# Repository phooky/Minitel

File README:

General instructions for using the minitel over a serial port:

- Set up and open a serial connection to the minitel. If you've put the 
minitel in 4800 baud mode (say, with Fn-B 4), then:
  minicom -D /dev/ttyUSB0 -b 4800
  Leave the connection open by exiting with Ctrl-A J.
- Set the tty to do newline processing correctly
  stty opost onlcr icrnl </dev/ttyUSB0
- Run whatever
  adventure </dev/ttyUSB0 >/dev/ttyUSB0

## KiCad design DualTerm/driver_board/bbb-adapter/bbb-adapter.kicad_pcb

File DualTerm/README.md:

Framebuffer
===========

The tilcdc driver provides a framebuffer on /dev/fb0. The resolution of this
framebuffer is 320x256. 
LAST COLUMN MUST BE SET TO 0 TO AVOID A BRIGHT LINE DURING ENTIRE HORIZ. RETRACT

Create fb0:
echo "MINITEL-TILCDC" >>/sys/devices/platform/bone_capemgr/slots

Detatch the console on fb0:
echo 0 >/sys/class/vtconsole/vtcon1/bind

Disable screen blanking:
echo 0 >/sys/class/graphics/fb0/blank

fbpad is build to default to fb0.

KERNEL VERSION:
debian@beaglebone:~$ cat /proc/version 
Linux version 4.4.36-ti-r72 (root@a2-imx6q-wandboard-2gb) (gcc version 4.9.2 (Debian 4.9.2-10) ) #1 SMP Wed Dec 7 22:29:53 UTC 2016
debian@beaglebone:~$ lsb -a
-bash: lsb: command not found
debian@beaglebone:~$ lsb
lsblk        lsb_release  
debian@beaglebone:~$ lsb_release -a
No LSB modules are available.
Distributor ID: Debian
Description:    Debian GNU/Linux 8.6 (jessie)
Release:    8.6
Codename:   jessie

Warning: there is a newer version with missing capemgr!

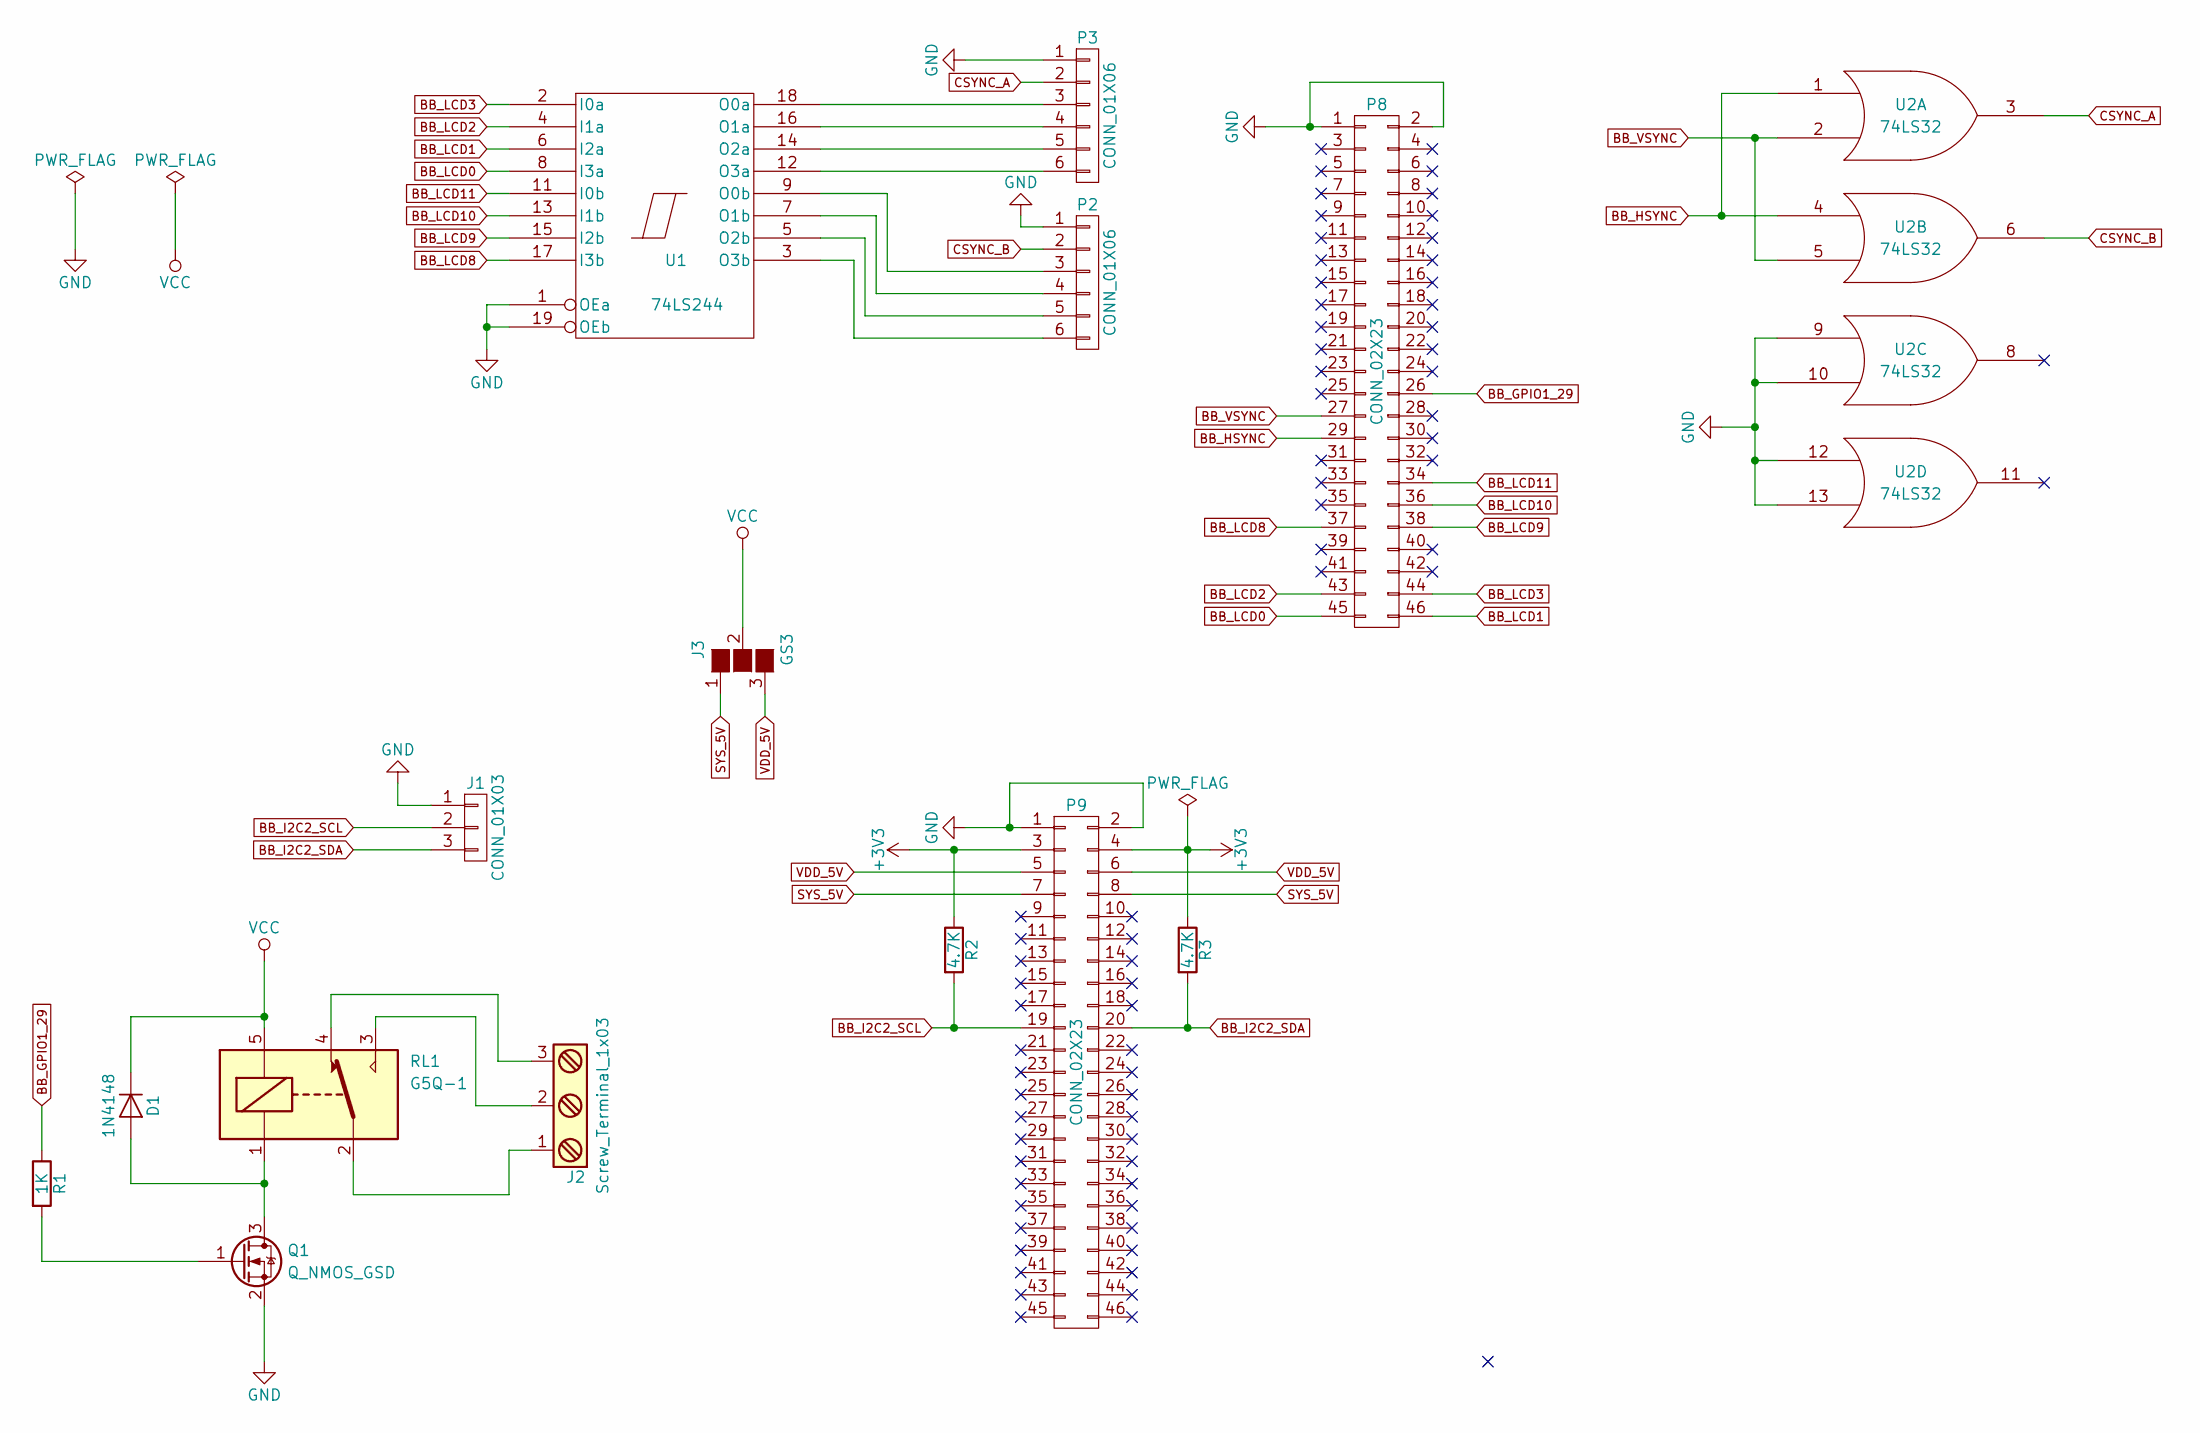
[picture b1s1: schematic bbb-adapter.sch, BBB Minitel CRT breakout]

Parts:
D1: 1N4148; D_DO-35_SOD27_P10.16mm_Horizontal
J1: CONN_01X03; Pin_Header_Angled_1x03_Pitch2.54mm
J2: Screw_Terminal_1x03; TerminalBlock_Pheonix_MKDS1.5-3pol
J3: GS3
P2, P3: CONN_01X06; Pin_Header_Angled_1x06_Pitch2.54mm
P8, P9: CONN_02X23; Pin_Header_Straight_2x23_Pitch2.54mm
Q1: Q_NMOS_GSD; SOT-23_Handsoldering
R1: 1K; R_Axial_DIN0207_L6.3mm_D2.5mm_P7.62mm_Horizontal
R2, R3: 4.7K; R_Axial_DIN0207_L6.3mm_D2.5mm_P7.62mm_Horizontal
RL1: G5Q-1; Relay_SPDT_OMRON-G5Q
U1: 74LS244; DIP-20_W7.62mm_LongPads
U2: 74LS32; DIP-14_W7.62mm_LongPads

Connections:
+3V3: P9.3, P9.4, R2.1, R3.1
BB_GPIO1_29: P8.26, R1.1
BB_HSYNC: P8.29, U2.1, U2.4
BB_I2C2_SCL: J1.2, P9.19, R2.2
BB_I2C2_SDA: J1.3, P9.20, R3.2
BB_LCD0: P8.45, U1.8 (I3a)
BB_LCD1: P8.46, U1.6 (I2a)
BB_LCD2: P8.43, U1.4 (I1a)
BB_LCD3: P8.44, U1.2 (I0a)
BB_LCD8: P8.37, U1.17 (I3b)
BB_LCD9: P8.38, U1.15 (I2b)
BB_LCD10: P8.36, U1.13 (I1b)
BB_LCD11: P8.34, U1.11 (I0b)
BB_VSYNC: P8.27, U2.2, U2.5
CSYNC_A: P3.2, U2.3
CSYNC_B: P2.2, U2.6
GND: J1.1, P2.1, P3.1, P8.1, P8.2, P9.1, P9.2, Q1.2 (S), U1.1 (OEa), U1.10 (GND), U1.19 (OEb), U2.7 (GND), U2.9, U2.10, U2.12, U2.13
unnamed: D1.2 (A), Q1.3 (D), RL1.1
unnamed: J2.1, RL1.2
unnamed: J2.2, RL1.3
unnamed: J2.3, RL1.4
unnamed: P2.3, U1.9 (O0b)
unnamed: P2.4, U1.7 (O1b)
unnamed: P2.5, U1.5 (O2b)
unnamed: P2.6, U1.3 (O3b)
unnamed: P3.3, U1.18 (O0a)
unnamed: P3.4, U1.16 (O1a)
unnamed: P3.5, U1.14 (O2a)
unnamed: P3.6, U1.12 (O3a)
unnamed: Q1.1 (G), R1.2
SYS_5V: J3.1 (G1), P9.7, P9.8
VCC: D1.1 (K), J3.2 (G2), RL1.5, U1.20 (VCC), U2.14 (VCC)
VDD_5V: J3.3 (G3), P9.5, P9.6

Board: 2 copper layers, 15 parts (0 on the bottom side), 33 nets, no tracks yet.

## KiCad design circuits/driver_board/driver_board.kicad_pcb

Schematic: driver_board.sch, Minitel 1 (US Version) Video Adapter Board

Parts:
C1: 10nF; C_Rect_L7.5_W6.5_P5
C2: 100nF; C_Rect_L7.5_W6.5_P5
CX1: COAX; COAX-SHLD
D1, D2, D3, D4: 1N4148; Diode_DO-35_SOD27_Horizontal_RM10
L1: 20uH; INDUCTOR_V
P1: CONN_01X06; Pin_Header_Angled_1x06
P2: CONN_01X07; CONN-1x7-5mm-pitch
Q1: C5468; TO-92_Inline_Wide
R1: 680; Resistor_Horizontal_RM10mm
R2: 4K; Resistor_Horizontal_RM10mm
R3: 1.8K; Resistor_Horizontal_RM10mm
R4: 1K; Resistor_Horizontal_RM10mm
R5: 460; Resistor_Horizontal_RM10mm
R6: 620; Resistor_Horizontal_RM10mm
R7: 100; Resistor_Horizontal_RM10mm
R8: 1.2K; Resistor_Horizontal_RM10mm
R9, R10: 2.4K; Resistor_Horizontal_RM10mm
RV1, RV2, RV3, RV4, RV5: POT; Potentiometer_Cermet_CT-6EP
U1: 74LS244; DIP-20_W7.62mm
U2: 74HC04; DIP-14_W7.62mm
U3: 7805; TO-220_Neutral123_Vertical

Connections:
GND: C1.1, C2.1, CX1.2, CX1.3, P1.1, P2.4, U1.1, U1.10, U1.13, U1.15, U1.17, U1.19, U2.7 (GND), U3.2
unnamed: C1.2, P2.2, R8.1
unnamed: C2.2, P2.1, R9.1, R10.1
unnamed: CX1.1, R7.1
unnamed: D1.1 (K), D2.1 (K), D3.1 (K), D4.1 (K), R1.2
unnamed: D1.2 (A), U1.18, U2.1
unnamed: D2.2 (A), U1.16, U2.3
unnamed: D3.2 (A), U1.14, U2.5
unnamed: D4.2 (A), U1.12, U2.9
unnamed: L1.1, Q1.2 (B)
unnamed: P1.2, U1.11
unnamed: P1.3, U1.8
unnamed: P1.4, U1.6
unnamed: P1.5, U1.4
unnamed: P1.6, U1.2
unnamed: P2.3, U2.12
unnamed: P2.6, U3.1
unnamed: Q1.1 (C), R7.2, R9.2, R10.2
unnamed: Q1.3 (E), R8.2, RV1.2, RV2.2, RV3.2, RV4.2, RV5.2
unnamed: R1.1, U2.11
unnamed: R2.1, RV1.1
unnamed: R2.2, U2.2
unnamed: R3.1, RV2.1
unnamed: R3.2, U2.4
unnamed: R4.1, RV3.1
unnamed: R4.2, U2.6
unnamed: R5.1, RV4.1
unnamed: R5.2, U2.8
unnamed: R6.1, RV5.1
unnamed: R6.2, U2.10
SYNC: U1.9, U2.13
VCC: L1.2, U1.20, U2.14 (VCC), U3.3

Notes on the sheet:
Pots are all 500 ohm CT6EP501 trimmers
Coil is Wurth 744772200
All resistors are standard 1/4W

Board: 2 copper layers, 29 parts (1 on the bottom side), 32 nets, no tracks yet.

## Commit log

2013-05-02 initial checkin
2013-05-02 adding basic doc
2013-05-02 don't resend redundant color information (speedup)
2013-05-02 turning minitel into a proper library adding unit tests to brush up on my tdd
2013-05-02 clearScreen
2013-05-02 convert over to object in script
2013-05-02 add newline
2013-05-02 added send and recv
2013-05-02 adding textmode switching
2013-05-02 added textmode test
2013-05-02 added and tested colors
2013-05-02 add vt mode switching
2013-05-02 cursor movement added
2013-05-02 fixup on test (text coords are 1-indexed)
2013-05-02 OMG MY SUBPIXEL ORDERING WAS OFF I AM SOOO EMBARRASSED
2013-05-03 tumblr image->minitel script
2013-05-06 reorganize image conversion in prep for menuing system
2013-05-07 adding screen reader
2013-05-07 move key to a json file
2013-05-23 added interactive mode added show/hide cursor added readline()
2013-05-25 update doc
2013-06-15 get port for command line
2013-06-15 oops; do port as env instead
2013-06-15 no sleep
2013-09-23 adding readme for general use
2013-09-27 adding cad files for NYCR "information terminal".
2013-09-27 adding top-level menuing system for minitel information service
2013-09-28 w/ curses emulation
2013-09-28 menuing system tested
2013-09-29 successfully running subprocesses (test case: /usr/games/adventure)
2013-09-29 added timeouts; default to 10 minutes without interaction.
2013-09-29 extend default timeout to ten minutes; test tinymush via terminal
2013-09-30 sim only if port is set to SIM
2013-09-30 default to ansi mode
2013-10-02 Update Readme.md
    Merged the information in README into this file
2013-10-02 Delete README
    Merged info into existing readme
2013-10-02 Update Readme.md
    Formatting
2013-10-02 adding cut file for top
2013-10-03 added support for various hax
2013-10-03 no room for wide, use tall
2013-10-03 move log to log
2013-10-04 lf/cr translation
2013-10-04 removing prints from library center title better colors
2013-10-04 adding game menu
2013-10-04 adding pager
2013-10-04 pager is running
2013-10-05 added sketch
2013-10-05 adding wakeup
2013-10-05 adding init script and readme
2013-10-05 run perpetually
2013-10-05 adding wait-for-key
2013-10-05 needed shell line
2013-10-05 fix pager keys, no 0 out of main menu, no immediate restart on timeout
2013-10-07 creating new format, parser
2013-10-08 menus working
2013-10-08 doc and screen up
2013-10-08 fix cli parse oops
2013-10-08 adding directions to pager
2013-10-08 clean up colors
2013-10-08 invalidate colors on clear; inverse text breadcrumbs
2013-10-08 adding runtime stuff again
2013-10-08 removing redundant file
2013-10-08 mode switching
2013-10-09 mode switching fixes
2013-10-09 minor fixups, cosmetic and otherwise
2013-10-10 added google calendar
2013-10-10 fixed run process
2013-10-11 refactoring tumblr for infoterm
2013-10-11 adding in tumblr screen
2013-10-12 adding maps
2013-10-12 cropped map
2013-10-12 adding non-scaling options
2013-10-13 change %screen to %layout
2013-10-13 removing timeout from menu
2013-10-13 adding layout class
2013-10-13 adding layout to type map
2013-10-13 B/W map to deal with color limitations
2013-10-13 testing, fixes for syntax issues, display issues
2013-10-13 adding echo key, test mode
2013-10-13 add 4 to test and kill extra keypress
2013-10-16 adding image caching (along with rep cache)
2013-10-16 fixed import
2013-10-18 fix calendar to handle private events
2013-10-18 ignore comments
2013-10-18 abbreviate pg
2013-10-18 reduce debug dump
2013-10-18 adding echo code
2013-12-01 update menus to add reboot
2017-04-05 adding video start
2017-04-07 continuing to reverse video output stage
2017-04-07 better video output stage diagram
2017-04-12 generated netlist; have actual transistor
2017-04-12 fixing 7805 symbol initial PCB layout quickly giving up on kicad
2017-04-14 adding test pattern generator
2017-04-15 getting rid of obsolete video kicad project
2017-04-15 circuit's pretty much done; now for a new board
2017-04-16 driver board initial checkin
2017-04-16 annotated and passed ERC
2017-04-16 most footprints associated; may need to make one for connector
2017-04-17 associating footprints with parts
2017-04-17 adding sample PRU project to test out basics on current version of BBB
2017-04-17 added footprint for 7 pin 5mm pitch header
2017-04-17 finally. Problems with the dts (ocp section missing) fixed.
2017-04-19 selecting pinmap for driving monitor
2017-04-19 starting in on proper driver
2017-04-19 *starting in on board *quick sync code
2017-04-19 first stab at sync signal
2017-04-19 changing dts file name to align with what we're actually doing
2017-04-19 generating inverted SYNC line
2017-04-21 directory rename to save some typing :P
2017-04-21 reformatting
2017-04-21 running into all kinds of roadblocks. should have done this in hardware. :P
2017-04-21 starting in on video driver
2017-04-21 looking into TI's LCDC driver. Maybe hack it to mono mode?
2017-04-21 changing name
2017-04-21 cobbling together several varieties of overlay to try to make something reasonable
2017-04-22 Continuing to work on dts for lcd
2017-04-24 first real stab at LCDC config
2017-04-24 Adding README Fixing syntax errors in DTS
2017-04-24 fixup for timing name in dts
2017-04-24 removing gpio, renumbering fragments
2017-04-24 Working (needed to choose a root dts w/o HDMI)
2017-04-26 adding some rough framebuffer stuff
2017-04-26 partial buffer fill test
2017-04-26 required fix_info for buffer len
2017-04-26 new timings for 320x200
2017-04-26 learning... interesting things
2017-04-26 moving to 360x260 reso
2017-04-26 fbtest to actual size
2017-04-26 reverted, centered, extended settings. maybe another 6 lines?
2017-04-26 pretty close to final timings
2017-04-28 Code reorganization
2017-04-28 adding first mockup roughing
2017-04-29 mockup and brackets
2017-05-05 updating test script
2017-05-08 fixup: high bits need to be set in the buffer.
2017-06-02 experimenting with a smaller display
2017-06-02 Didn't help. Going back to 320x200 Revert "experimenting with a smaller display"
    This reverts commit 153692669a218de988363964fecc591d21bd2ad7.
2017-06-14 adjusted timing to more reasonable settings after fixing timing issue in hardware
2017-07-04 adding bbb breakout board schematic
2017-07-05 getting bbb adapter to board layout stage
2017-07-05 initial PCB layout
2017-07-05 board ordered
2017-07-12 adding readme notes
